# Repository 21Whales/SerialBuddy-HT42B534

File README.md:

# SerialBuddy-HT42B534

[Schematics/Board](https://kicanvas.org/?github=https%3A%2F%2Fgithub.com%2F21Whales%2FSerialBuddy-HT42B534%2Ftree%2Fmain%2Fhardware%2Frev1)

## Overview

SerialBuddy-HT42B534 is a USB to UART interface based on the Holtek HT42B534 chip, designed with a focus on simplicity and versatility. It is suitable for breadboard use, featuring clearly labeled pins and supporting dual voltage supply (3.3V and 5V). The device also offers selectable I/O voltage (3.3V or 5V), and excludes less commonly used pins like RTS and CTS for a streamlined user experience. SerialBuddy-HT42B534 is an open-source hardware project distributed under the BSD 3-Clause License.

## Features

- USB to UART interface
- Breadboard-friendly design
- Clearly labeled pins for easy reference
- Dual voltage supply (3.3V and 5V)
- Selectable I/O voltage (3.3V or 5V)
- Excludes less commonly used pins like RTS and CTS for simplicity
- Open-source hardware under BSD 3-Clause License

## Pin Names

- **TX**: Transmit Data
- **RX**: Receive Data
- **GND**: Ground
- **VDD**: Power Supply (Selectable: 3.3V or 5V)
- **VBUS**: 5V from USB Bus
- **3V3**: 3.3V from internal regulator

## License

SerialBuddy-HT42B534 is distributed under the [BSD 3-Clause License](LICENSE).

## Contributing

We welcome contributions! Feel free to submit bug reports, feature requests, or pull requests.

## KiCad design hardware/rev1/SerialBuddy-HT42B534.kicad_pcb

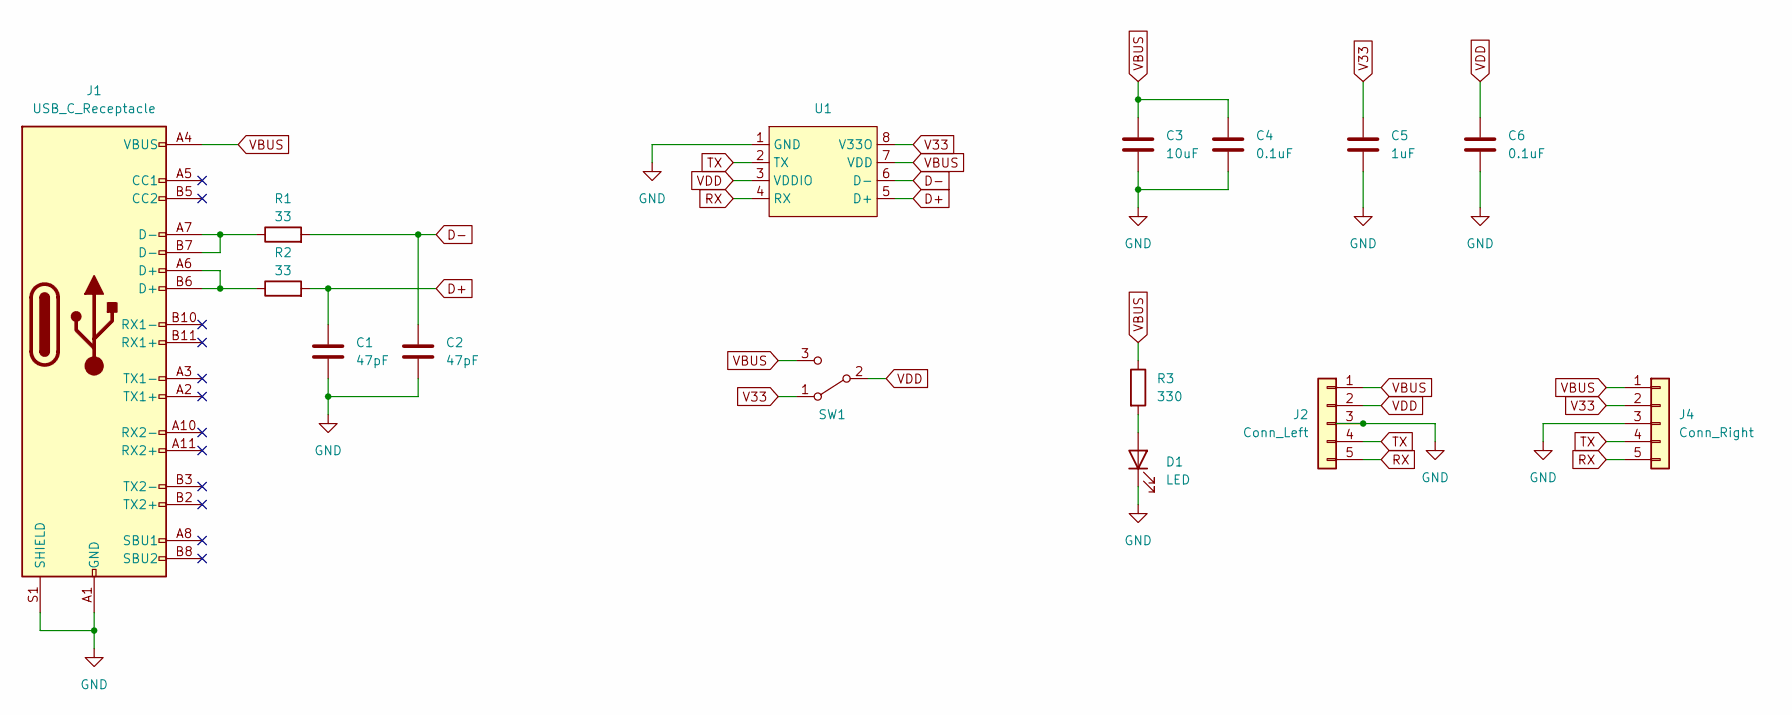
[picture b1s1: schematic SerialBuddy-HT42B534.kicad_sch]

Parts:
C1, C2: 47pF; C_0402_1005Metric; LCSC C1567
C3: 10uF; C_0402_1005Metric; LCSC C15525
C4, C6: 0.1uF; C_0402_1005Metric; LCSC C1525
C5: 1uF; C_0402_1005Metric; LCSC C52923
D1: LED; LED_0402_1005Metric; LCSC C434449
J1: USB_C_Receptacle; USB_C_Receptacle_G-Switch_GT-USB-7010ASV; LCSC C2988369
J2: Conn_Left; Conn_1x05
J4: Conn_Right; Conn_1x05
R1, R2: 33; R_0402_1005Metric; LCSC C25105
R3: 330; R_0402_1005Metric; LCSC C25104
SW1: SW_SPDT; MSS12C02; LCSC C3008585
U1: SO-8_3.9x4.9mm_P1.27mm; LCSC C493294

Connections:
D+: C1.1, R2.2, U1.5 (D+)
D-: C2.1, R1.2, U1.6 (D-)
GND: C1.2, C2.2, C3.2, C4.2, C5.2, C6.2, D1.1 (K), J1.A1 (GND), J1.A12 (GND), J1.B1 (GND), J1.B12 (GND), J1.S1 (SHIELD), J2.3, J4.3, U1.1 (GND)
unnamed: D1.2 (A), R3.2
unnamed: J1.A6 (D+), J1.B6 (D+), R2.1
unnamed: J1.A7 (D-), J1.B7 (D-), R1.1
RX: J2.5, J4.5, U1.4 (RX)
TX: J2.4, J4.4, U1.2 (TX)
V33: C5.1, J4.2, SW1.1 (A), U1.8 (V33O)
VBUS: C3.1, C4.1, J1.A4 (VBUS), J1.A9 (VBUS), J1.B4 (VBUS), J1.B9 (VBUS), J2.1, J4.1, R3.1, SW1.3 (C), U1.7 (VDD)
VDD: C6.1, J2.2, SW1.2 (B), U1.3 (VDDIO)

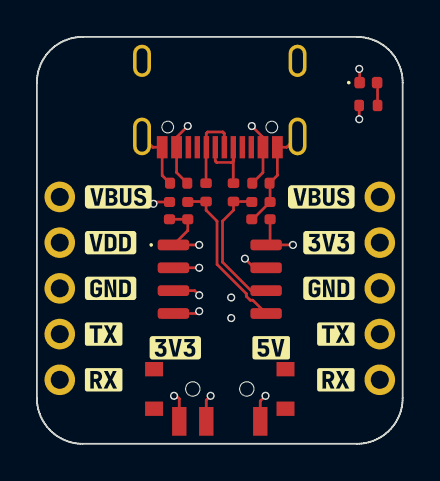
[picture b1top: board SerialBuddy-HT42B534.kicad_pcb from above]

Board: 4 copper layers, 20.3 x 22.6 mm, 15 parts (0 on the bottom side), 11 nets.

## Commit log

2023-12-17 add files
2023-12-17 add usb plug 3d model
2023-12-17 add readme
2023-12-17 update solder mask to say 3V3 instead of 3.3V or V33
2023-12-17 add image
2023-12-17 add link to board/schematics
2024-01-08 fix label
